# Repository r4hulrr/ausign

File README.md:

# AUSIGN – Real-Time Auslan Sign Language Interpreter

 **Breaking communication barriers** for the Australian Deaf community with an affordable, wearable, real-time Auslan-to-speech translation glove. Check out the [demo video](https://drive.google.com/file/d/1WPN_qFuqe7VqrdAuftsNLOaqI1UlMCOe/view?usp=sharing).

## Overview
**AUSIGN** is a wearable assistive technology device designed to translate **Australian Sign Language (Auslan)** into spoken English **in real time**, enabling smoother and more natural communication for deaf and non-verbal individuals.

Unlike existing ASL-centric devices, AUSIGN is **purpose-built for Auslan**, incorporating contextual awareness via a heart-rate sensor, low-latency audio feedback, and Bluetooth connectivity for flexible output through a mobile/desktop app.

##  Key Features
- **Auslan-specific design** – recognises grammar and gestures unique to Auslan.
- **Context-aware translation** – heartbeat sensing to infer emotional tone.
- **Low-latency output** – low latency translation for natural conversations.
- **Comfort & portability** – under 150 g, designed for all-day wear.
- **Cross-platform UI** – BLE-connected Python GUI.
- **Rechargeable & all-day battery life** – ~6 hours continuous operation.

## System Architecture

**High Level Diagram**

**Hardware**
- **Sensors:**  
  - 5× flex sensors for finger bend detection  
  - LSM6DSOTR 6-axis IMU for hand motion/orientation  
  - MAX30105 heartbeat sensor for emotional context  
- **Processing:** ESP32-S3 microcontroller with BLE & I²S audio output  
- **Output:** OLED display + speaker (via MAX98357A DAC/amp), 2× customisable push buttons  
- **Power:** 3.7 V Li-Po battery with BQ24074 power management & charging

**Software**
- **Firmware:** Reads sensor data, sends via BLE to host app, plays audio from internal flash.  
- **Recognition algorithm:** Condition-matching engine using flex, IMU, and BPM thresholds from CSV definitions.  
- **GUI:** Python-based BLE interface for displaying recognised signs, sensor status, and audio playback.  

## Repository Structure
```
├── firmware/ # ESP32-S3 C++ firmware (Arduino/ESP-IDF)
│ ├── src # Contains the main esp32 code along with test code for every component
│ ├── partitions # Custom partition implemented for our 16MB Flash size
├── gui/ # Python BLE GUI application
│ ├── frontend.py # main GUI script
│ ├── signs.csv # Sign definition mappings
│ └── ...
├── hardware/ # PCB schematics and board layouts
│ ├── main_board/
│ ├── breakout_board/
├── demo # Demo video
│ ├── demo_video.mp4
├── docs/ # design docs
└── LICENSE
└── README.md
```

## Demo
Check out the [demo video](demo/demo_video.mov) to see AUSIGN in action.

## License
This project is licensed under the [MIT License](LICENSE).

## Authors
- **Rahul Ramachandran** 
- **Enzo Moriguchi** 

---
> *“Technology is best when it brings people together.”* – AUSIGN aims to bridge the communication gap and foster inclusion through engineering innovation.

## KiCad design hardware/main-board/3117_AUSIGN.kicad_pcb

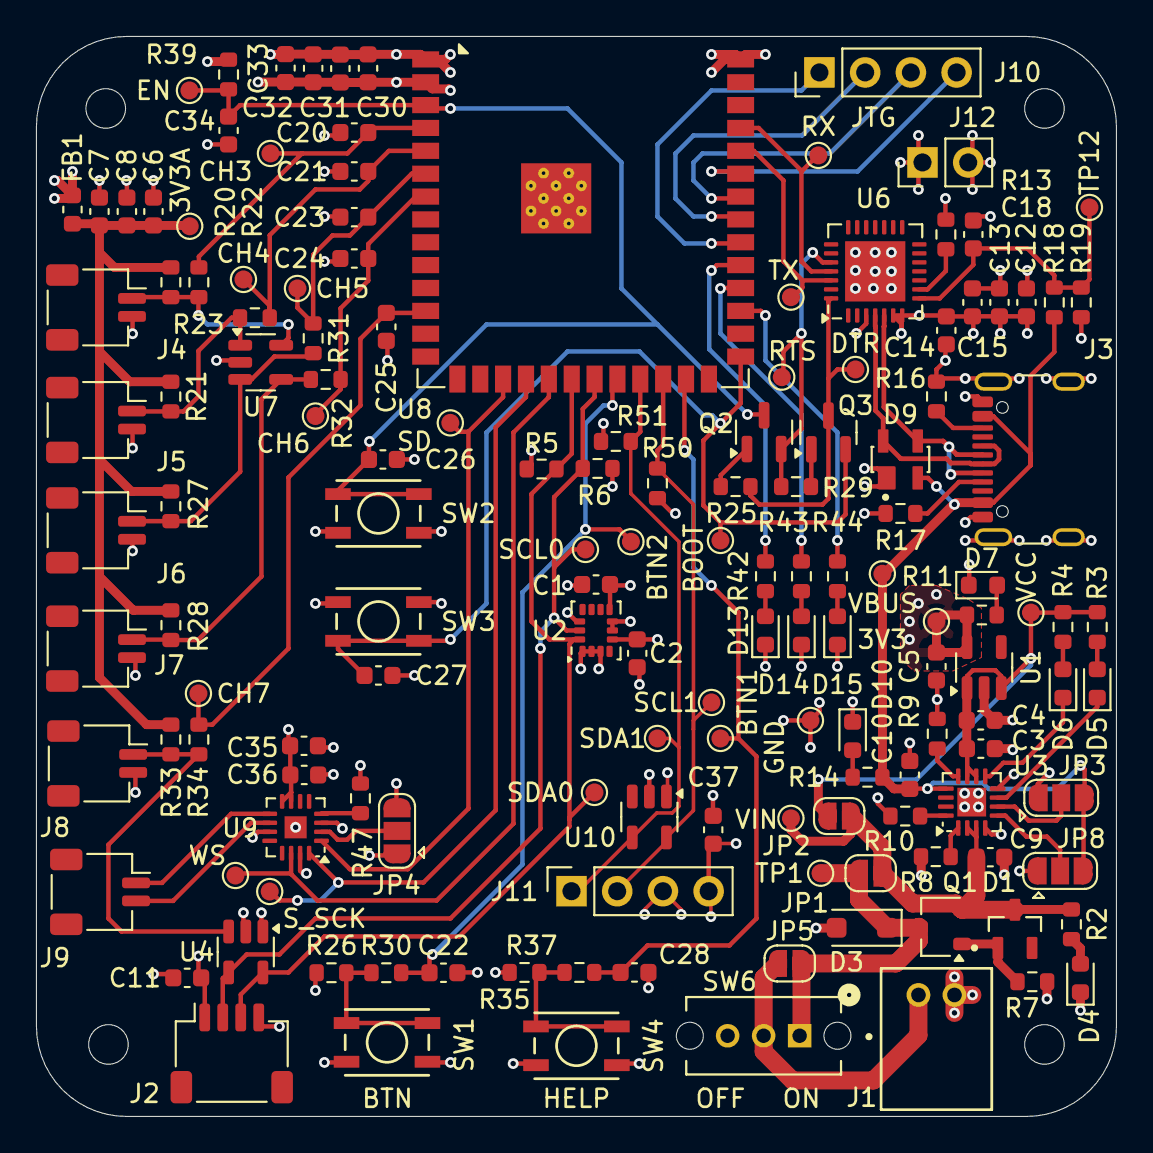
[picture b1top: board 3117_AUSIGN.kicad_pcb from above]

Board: 4 copper layers, 60.0 x 60.0 mm, 151 parts (0 on the bottom side), 70 nets.

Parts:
3V3, 3V3A: TestPoint; TestPoint_Pad_D1.0mm
BOOT: TestPoint; TestPoint_Pad_D1.0mm
BTN1, BTN2: TestPoint; TestPoint_Pad_D1.0mm
C1, C2, C7, C8, C11, C14, C15, C20, C21, C22, C23, C24, C25, C26, C27, C28, C30, C31, C36, C37: 100n; C_0603_1608Metric
C3, C9, C12, C13: 4u7; C_0603_1608Metric
C4, C5, C10, C18, C34: 1u; C_0603_1608Metric
C6, C35: 10u; C_0603_1608Metric
C32, C33: 22u; C_0603_1608Metric
CH3, CH4, CH5, CH6, CH7: TestPoint; TestPoint_Pad_D1.0mm
D1: MMBZ5233BLT1G
D3: SMF5.0A; D_SOD-123F
D4, D7, D10: LTST-C190KGKT; LED_0603_1608Metric
D5, D6, D13, D14, D15: LTST-C190KFKT; LED_0603_1608Metric
D9: SP0503BAHT; SP0503BAHTG
DTR: TestPoint; TestPoint_Pad_D1.0mm
EN: TestPoint; TestPoint_Pad_D1.0mm
FB1: BLM18AG601SN1D; L_0603_1608Metric
GND: TestPoint; TestPoint_Pad_D1.0mm
H1, H2, H3, H4: MountingHole; MountingHole_2.2mm_M2
J1: JST_PH_2P
J2: JST_SH_4P; JST_SH_SM04B-SRSS-TB_1x04-1MP_P1.00mm_Horizontal
J3: USB4105-GF-A; USB_C_Receptacle_GCT_USB4105-xx-A_16P_TopMnt_Horizontal
J4, J5, J6, J7, J8, J9: JST_SH_2P; JST_SH_SM02B-SRSS-TB_1x02-1MP_P1.00mm_Horizontal
J10: Conn_01x04_Pin; PinHeader_1x04_P2.54mm_Vertical
J11: Conn_01x04_Socket; PinSocket_1x04_P2.54mm_Vertical
J12: Conn_01x02_Pin; PinHeader_1x02_P2.54mm_Vertical
JP1, JP2, JP5: SolderJumper_2_Open; SolderJumper-2_P1.3mm_Open_RoundedPad1.0x1.5mm
JP3, JP4, JP8: SolderJumper_3_Open; SolderJumper-3_P1.3mm_Open_RoundedPad1.0x1.5mm
Q1: IRLML6402TRPBF; SOT-23W
Q2, Q3: SS8050; SOT-23
R2, R3, R4: 499; R_0603_1608Metric
R5, R6, R50, R51: 4k7; R_0603_1608Metric
R7: 100k; R_0603_1608Metric
R8, R20, R21, R22, R23, R25, R26, R27, R28, R29, R31, R32, R33, R34, R35, R39: 10k; R_0603_1608Metric
R9, R10: 1.5k; R_0603_1608Metric
R11, R42, R43, R44: 200; R_0603_1608Metric
R13, R14, R30, R37: 1k; R_0603_1608Metric
R16, R17: 5k1; R_0603_1608Metric
R18: 22k1; R_0603_1608Metric
R19: 47k5; R_0603_1608Metric
R47: 634k; R_0603_1608Metric
RTS: TestPoint; TestPoint_Pad_D1.0mm
RX: TestPoint; TestPoint_Pad_D1.0mm
SCL0, SCL1: TestPoint; TestPoint_Pad_D1.0mm
SD: TestPoint; TestPoint_Pad_D1.0mm
SDA0, SDA1: TestPoint; TestPoint_Pad_D1.0mm
SW1, SW2, SW3, SW4: PTS815SJK250SMTR
SW6: OS102011MS2QN1
S_SCK: TestPoint; TestPoint_Pad_D1.0mm
TP1, TP12: TestPoint; TestPoint_Pad_D1.0mm
TX: TestPoint; TestPoint_Pad_D1.0mm
U1: AP2112K-3.3; SOT-23-5
U2: LSM6DSOTR; LGA-14_3x2.5mm_P0.5mm_LayoutBorder3x4y
U3: BQ24074RGT; VQFN-16-1EP_3x3mm_P0.5mm_EP1.6x1.6mm
U4, U7, U10: ESDS314DBVR; SOT-23-5
U6: CP2102N-A02-GQFN28; QFN-28-1EP_5x5mm_P0.5mm_EP3.35x3.35mm
U8: ESP32-S3-WROOM-1
U9: MAX98357A; TQFN-16-1EP_3x3mm_P0.5mm_EP1.23x1.23mm
VBUS: TestPoint; TestPoint_Pad_D1.0mm
VCC: TestPoint; TestPoint_Pad_D1.0mm
VIN: TestPoint; TestPoint_Pad_D1.0mm
WS: TestPoint; TestPoint_Pad_D1.0mm

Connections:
+3V3: 3V3.1, C1.1, C2.1, C5.1, C11.1, C12.1, C13.1, C14.1, C15.1, C30.1, C31.1, C32.1, C33.1, C35.1, C36.1, C37.1, FB1.1, J2.1, J11.4, J12.1, JP4.3 (B), R5.1, R6.1, R11.1, R13.1, R26.1, R35.1, R39.1, R47.1, R50.2, R51.2, U1.5 (VOUT), U2.5 (VDDIO), U2.8 (VDD), U2.12 (CS), U4.1 (I/O1), U6.6 (VDD), U6.7 (VREGIN), U8.2 (3V3), U9.7 (VDD), U9.8 (VDD), U10.1 (I/O1)
+3V3A: 3V3A.1, C6.1, C7.1, C8.1, FB1.2, R20.1, R21.1, R27.1, R28.1, R33.1
ADC1_CH3: C20.1, CH3.1, R22.1, U8.4 (IO4)
ADC1_CH4: C21.1, CH4.1, R23.1, U8.5 (IO5)
ADC1_CH5: C23.1, CH5.1, R31.1, U8.6 (IO6)
ADC1_CH6: C24.1, CH6.1, R32.1, U8.7 (IO7)
ADC1_CH7: C25.1, CH7.1, R34.1, U8.12 (IO8)
BOOT: BOOT.1, C27.1, Q3.2 (E), SW3.2 (B), U8.27 (IO0)
BTN1: BTN1.1, C28.1, R37.1, U8.25 (IO48)
BTN2: BTN2.1, C22.1, R30.1, U8.22 (IO14)
CH3: J4.1, R20.2, R22.2, U7.5 (I/O4)
CH4: J5.1, R21.2, R23.2, U7.1 (I/O1)
CH5: J6.1, R27.2, R31.2, U7.3 (I/O2)
CH6: J7.1, R28.2, R32.2, U7.4 (I/O3)
CH7: J8.1, R33.2, R34.2, U4.3 (I/O2)
DTR: DTR.1, Q3.3 (C), R25.1, U6.28 (~DTR)
EN: C26.1, C34.1, EN.1, Q2.3 (C), R39.2, SW2.2 (B), U8.3 (EN)
GND: C1.2, C2.2, C3.2, C4.2, C5.2, C6.2, C7.2, C8.2, C9.2, C10.2, C11.2, C12.2, C13.2, C14.2, C15.2, C18.2, C20.2, C21.2, C22.2, C23.2, C24.2, C25.2, C26.2, C27.2, C28.2, C30.2, C31.2, C32.2, C33.2, C34.2, C35.2, C36.2, C37.2, D3.2 (A), D4.1 (K), D7.1 (K), D9.1 (A), D10.1 (K), D13.1 (K), D14.1 (K), D15.1 (K), GND.1, J1.2, J2.4, J3.A1 (GND), J3.A12 (GND), J3.B1 (GND), J3.B12 (GND), J3.S1 (SHIELD), J4.2, J5.2, J6.2, J7.2, J8.2, J11.3, J12.2, JP3.1 (A), JP4.1 (A), JP8.1 (A), R7.2, R8.2, R9.2, R10.2, R16.2, R17.2, R19.2, SW1.1 (A), SW2.1 (A), SW3.1 (A), SW4.1 (A), U1.2 (GND), U2.1 (SDO/SA0), U2.2 (SDX), U2.3 (SCX), U2.6 (GND), U2.7 (GND), U3.4 (~CE), U3.8 (VSS), U3.17 (VSS), U4.2 (GND), U6.3 (GND), U6.29 (GND), U7.2 (GND), U8.1 (GND), U8.40 (GND), U8.41 (GND), U9.3 (GND), U9.11 (GND), U9.15 (GND), U9.17 (PAD), U10.2 (GND)
I2C0_SCL: J2.2, R6.2, SCL0.1, U2.13 (SCL), U4.4 (I/O3), U8.21 (IO13)
I2C0_SDA: J2.3, R5.2, SDA0.1, U2.14 (SDA), U4.5 (I/O4), U8.20 (IO12)
I2C1_SCL: J11.2, R50.1, SCL1.1, U8.24 (IO47), U10.5 (I/O4)
I2C1_SDA: J11.1, R51.1, SDA1.1, U8.23 (IO21), U10.4 (I/O3)
I2S_SCK: S_SCK.1, U8.18 (IO10), U9.16 (BCLK)
I2S_SD: SD.1, U8.17 (IO9), U9.1 (DIN)
I2S_WS: U8.19 (IO11), U9.14 (LRCLK), WS.1
LED3: R42.1, U8.31 (IO38)
LED4: R43.1, U8.30 (IO37)
LED5: R44.1, U8.29 (IO36)
unnamed: D1.1 (A), Q1.1 (G), R7.1
unnamed: D3.1 (K), JP1.1 (A), JP5.2 (B), Q1.3 (D), SW6.1 (A), TP1.1
unnamed: D4.2 (A), R2.2
unnamed: D5.2 (A), R3.2
unnamed: D5.1 (K), U3.7 (~PGOOD)
unnamed: D6.2 (A), R4.2
unnamed: D6.1 (K), U3.9 (~CHG)
unnamed: D7.2 (A), R11.2
unnamed: D10.2 (A), R14.2
unnamed: D13.2 (A), R42.2
unnamed: D14.2 (A), R43.2
unnamed: D15.2 (A), R44.2
unnamed: J1.1, JP5.1 (A), SW6.2 (B)
unnamed: J3.A5 (CC1), R17.1
unnamed: J3.B5 (CC2), R16.1
unnamed: J9.1, U9.9 (OUTP)
unnamed: J9.2, U9.10 (OUTN)
unnamed: JP3.2 (C), U3.6 (EN1)
unnamed: JP4.2 (C), U9.2 (GAIN_SLOT)
unnamed: JP8.2 (C), U3.5 (EN2)
unnamed: Q2.1 (B), R25.2
unnamed: Q3.1 (B), R29.2
unnamed: R26.2, R30.2, SW1.2 (B)
unnamed: R35.2, R37.2, SW4.2 (B)
unnamed: R9.1, U3.12 (ILIM)
unnamed: R10.1, U3.16 (ISET)
unnamed: R8.1, U3.1 (TS)
unnamed: C18.1, R18.2, R19.1, TP12.1, U6.8 (VBUS)
unnamed: R13.2, U6.9 (~RST)
unnamed: R47.2, U9.4 (~SD_MODE)
RTS: Q2.2 (E), R29.1, RTS.1, U6.24 (~RTS)
RXD0: RX.1, U6.25 (RXD), U8.37 (TXD0)
TCK: J10.1, U8.32 (IO39)
TDI: J10.3, U8.34 (IO41)
TDO: J10.2, U8.33 (IO40)
TMS: J10.4, U8.35 (IO42)
TXD0: TX.1, U6.26 (TXD), U8.36 (RXD0)
USB_DN: D9.3 (K), J3.A7 (D-), J3.B7 (D-), U6.5 (D-)
USB_DP: D9.4 (K), J3.A6 (D+), J3.B6 (D+), U6.4 (D+)
VBUS: C10.1, D9.2 (K), J3.A4 (VBUS), J3.A9 (VBUS), J3.B4 (VBUS), J3.B9 (VBUS), JP3.3 (B), JP8.3 (B), R14.1, R18.1, U3.13 (IN), VBUS.1
VCC: C3.1, C4.1, JP2.2 (B), R3.1, R4.1, U1.1 (VIN), U1.3 (EN), U3.10 (OUT), U3.11 (OUT), VCC.1
Vin: C9.1, D1.3 (K), JP1.2 (B), JP2.1 (A), Q1.2 (S), R2.1, U3.2 (BAT), U3.3 (BAT), VIN.1

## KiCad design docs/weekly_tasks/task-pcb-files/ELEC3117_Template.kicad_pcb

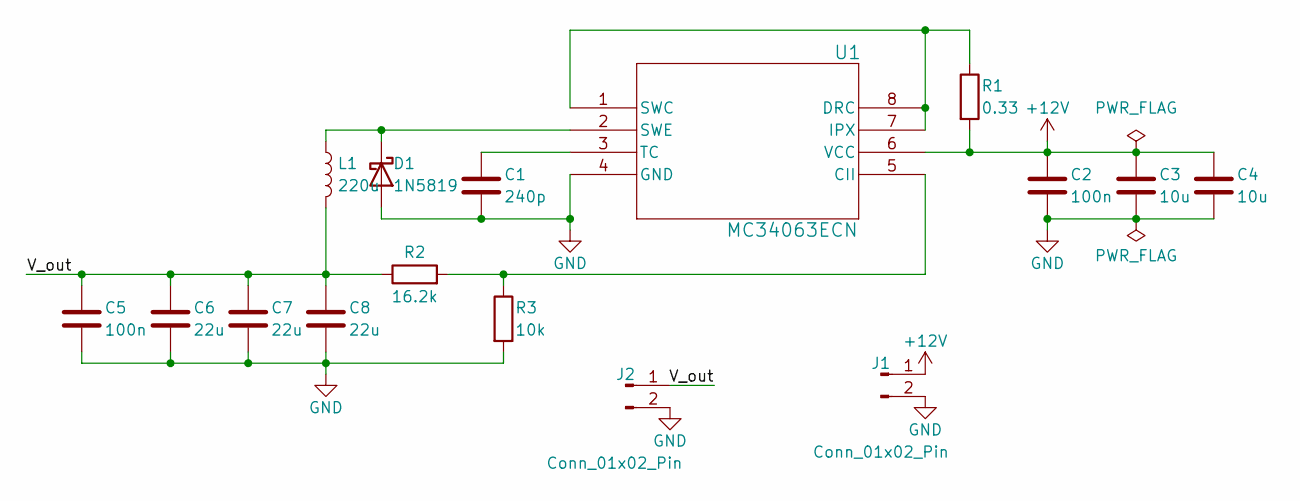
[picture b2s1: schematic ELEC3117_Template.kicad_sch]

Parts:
C1: 240p; C_0805_2012Metric
C2, C5: 100n; C_0805_2012Metric
C3, C4: 10u; C_0805_2012Metric
C6, C7, C8: 22u; C_0805_2012Metric
D1: 1N5819; D_DO-41_SOD81_P10.16mm_Horizontal
J1, J2: Conn_01x02_Pin; PinHeader_1x2_2.54mm_Vertical
L1: 220u; IND_RCH8011_SUM
R1: 0.33; R_0805_2012Metric
R2: 16.2k; R_0805_2012Metric
R3: 10k; R_0805_2012Metric
U1: MC34063ECN; DIP-8_STM

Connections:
+12V: C2.1, C3.1, C4.1, J1.1, R1.2, U1.6 (VCC)
/V_out: C5.1, C6.1, C7.1, C8.1, J2.1, L1.2, R2.1
GND: C1.2, C2.2, C3.2, C4.2, C5.2, C6.2, C7.2, C8.2, D1.2 (A), J1.2, J2.2, R3.2, U1.4 (GND)
unnamed: D1.1 (K), L1.1, U1.2 (SWE)
unnamed: R2.2, R3.1, U1.5 (CII)
unnamed: R1.1, U1.1 (SWC), U1.7 (IPX), U1.8 (DRC)
unnamed: C1.1, U1.3 (TC)

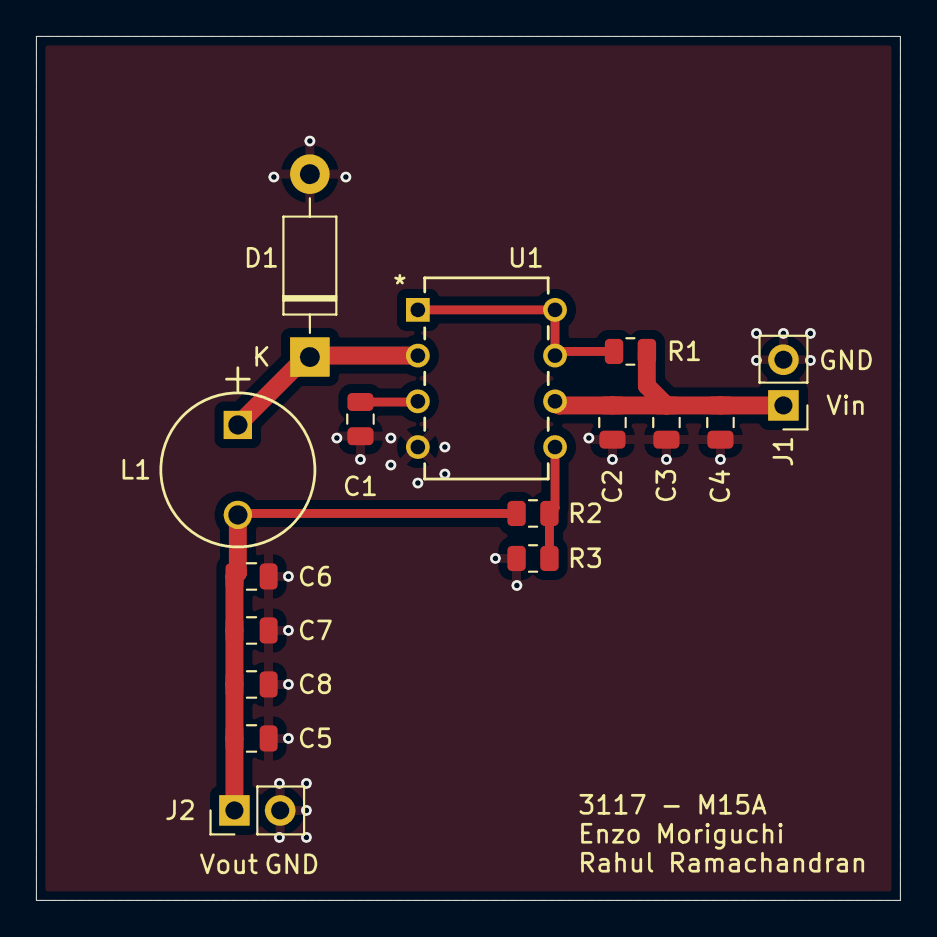
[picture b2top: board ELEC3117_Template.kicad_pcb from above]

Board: 2 copper layers, 48.0 x 48.0 mm, 16 parts (0 on the bottom side), 7 nets.

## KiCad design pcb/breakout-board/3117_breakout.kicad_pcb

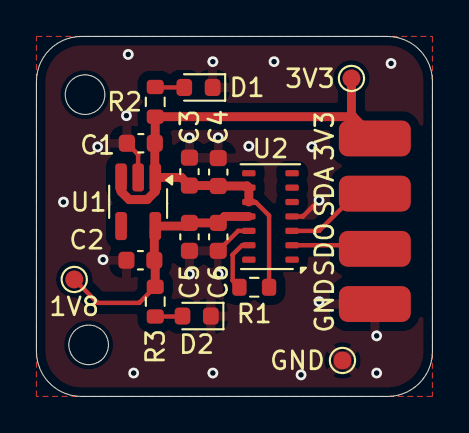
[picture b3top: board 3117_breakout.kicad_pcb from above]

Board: 2 copper layers, 22.0 x 20.0 mm, 19 parts (0 on the bottom side), 8 nets.

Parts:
1V8, 3V3: TestPoint; TestPoint_Pad_D1.0mm
C1: 1u; C_0603_1608Metric
C2: 0.47u; C_0603_1608Metric
C3: 10u; C_0603_1608Metric
C4, C6: 100n; C_0603_1608Metric
C5: 4u7; C_0603_1608Metric
D1: LTST-C190KGKT; LED_0603_1608Metric
D2: 5988E40107F; LED_0603_1608Metric
GND: TestPoint; TestPoint_Pad_D1.0mm
H1, H2: MountingHole; MountingHole_2.2mm_M2
J1: Conn_01x04_Pin; JST_SH_SM04B-SRSS-TB_1x04-1MP_P1.00mm_Horizontal
R1: 4k7; R_0603_1608Metric
R2: 200; R_0603_1608Metric
R3: 49.9; R_0603_1608Metric
U1: TLV77018PDBVR; SOT-23-5_HandSoldering
U2: MAX30102; Maxim_OLGA-14_3.3x5.6mm_P0.8mm

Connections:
+1V8: 1V8.1, C2.1, C5.1, C6.1, R3.1, U1.5 (OUT), U2.11 (VDD)
+3V3: 3V3.1, C1.1, C3.1, C4.1, J1.4, R1.1, R2.1, U1.1 (IN), U1.3 (EN), U2.9 (VLED+), U2.10 (VLED+)
GND: C1.2, C2.2, C3.2, C4.2, C5.2, C6.2, D1.1 (K), D2.1 (K), GND.1, J1.1, U1.2 (GND), U2.4 (PGND), U2.12 (GND)
I2C0_SCL: J1.2, U2.2 (SCL)
I2C0_SDA: J1.3, U2.3 (SDA)
unnamed: D1.2 (A), R2.2
unnamed: D2.2 (A), R3.2
unnamed: R1.2, U2.13 (~INT)

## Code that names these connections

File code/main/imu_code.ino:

// Default Arduino Libraries
#include <Arduino.h>
#include <Wire.h>
#include <SPI.h>
#include <SD.h>

// Libraries to download from Arduino IDE
#include <RTClib.h>
#include <Adafruit_MAX31855.h>
#include <Adafruit_BME280.h>
#include <Adafruit_LSM6DS3TRC.h> // use this for the breakout board
#include <Adafruit_LSM6DSOX.h> // use this for the actual IC

// Constants
#define MAX_READS 2000
#define STORE_ONBOARD_DELAY 5 // In sec
#define PRINT_SAMPLE_DELAY 5 // In sec
#define THERMAL_DELAY 20  // In milliseconds
#define REQUEST_DELAY 100  // In milliseconds
#define OUTPUT_REPEAT_DELAY 15 // In sec
#define SD_OUTPUT_DELAY 1 // In sec
#define SERIAL_SPEED 115200
#define MIN_TEMP -10 
#define MAX_TEMP 10
#define MIN_OUTPUT_REQUESTS 5
#define NUM_BME 4
#define NUM_IMU 2
#define NUM_I2C 2
#define NUM_DIM 3
#define RTC_LINE 0
#define SD_DET_PIN 4
#define SPI1_SO 12
#define SPI1_CSN 9
#define SPI1_SCK 14
#define SPI1_SI 15
#define SPI0_SO 16
#define SPI0_CSN 17
#define SPI0_SCK 18
#define I2C0_SDA 20
#define I2C0_SCL 21 
#define I2C1_SDA 26
#define I2C1_SCL 27 
#define CSN_SD2  13// Select for SD cards, GP22
#define OFFLOAD_TRIGGER 0 // Jumper cable GP12 (Pin 16) to GP13 (Pin 17) to request data offload
#define HEATER_PIN 22 // GP22 (Pin 29)

// Initialise I2C lines
TwoWire TwoWire1 = TwoWire(i2c0, I2C0_SDA, I2C0_SCL);
TwoWire TwoWire2 = TwoWire(i2c1, I2C1_SDA, I2C1_SCL);
TwoWire* Wires[NUM_I2C] = {&TwoWire1 , &TwoWire2};


// Initialise IMUs
Adafruit_LSM6DS3TRC imu[NUM_IMU];
Adafruit_LSM6DSOX imu[NUM_IMU];


TPHReading tphData[NUM_BME][MAX_READS];     // Memory size is NUM_BME * MAX_READS * 3 * 32
AGReading agData[NUM_IMU][MAX_READS];       // Memory size is NUM_IMU * MAX_READS * 6 * 32
double tcData[MAX_READS];                   // Memory size is MAX_READS * 64
DateTime timestamp[MAX_READS];              // Memory size is MAX_READS * 32    -> total is 21 * MAX_READS * 32 bits = 21 * MAX_READS * 4 bytes = 168 kB (for 2000 reads)
bool heaterStatus[MAX_READS];               // Memory size is MAX_READS


void i2cIMUattach() {
  for (int i = 0; i < NUM_IMU; i++) {
    Serial.print(String("Attempt IMU ") + i + String(" ------- "));

    if (!imu[i].begin_I2C((uint8_t)LSM6DS_I2CADDR_DEFAULT, Wires[i])) {
      Serial.println(String("IMU ") + i + String(" not found"));
      successful_setup = false;
    } else {
      Serial.println(String("IMU ") + i + String(" found"));
    }

    imu[i].setAccelRange(LSM6DS_ACCEL_RANGE_2_G);
    imu[i].setGyroRange(LSM6DS_GYRO_RANGE_250_DPS);
    //imu[i].setAccelDataRate(LSM6DS_RATE_12_5_HZ);
    //imu[i].setGyroDataRate(LSM6DS_RATE_12_5_HZ);
  }
}







AGReading getIMUData(int numIMU) {
  sensors_event_t accel_event, gyro_event, temp_event;

  imu[numIMU].getEvent(&(accel_event), &(gyro_event), &(temp_event));

  sensors_vec_t currAcc = accel_event.acceleration;
  sensors_vec_t currGyro = gyro_event.gyro;

  AGReading IMUData = {};

  IMUData.acc[0] = currAcc.x;
  IMUData.acc[1] = currAcc.y;
  IMUData.acc[2] = currAcc.z;
  IMUData.gyro[0] = currGyro.x;
  IMUData.gyro[1] = currGyro.y;
  IMUData.gyro[2] = currGyro.z;

  return IMUData;
}


void printCurrentDataEntry() {
  if (elapsed(millis(), &last_print, PRINT_SAMPLE_DELAY)) {

    for (int i = 0; i < NUM_IMU; i++) {
      Serial.println(String("IMU ") + i + String(" :"));
      Serial.print(agData[i][num_read].acc[0] + String(","));
      Serial.print(agData[i][num_read].acc[1] + String(","));
      Serial.println(agData[i][num_read].acc[2]);
      Serial.print(agData[i][num_read].gyro[0] + String(","));
      Serial.print(agData[i][num_read].gyro[1] + String(","));
      Serial.println(agData[i][num_read].gyro[2]);
    }

    Serial.println(String("Thermo: ") + tcData[num_read]);
    Serial.println(String("Time: ") + String(timestamp[num_read].hour()) + String(":") + String(timestamp[num_read].minute()) + String(":") + String(timestamp[num_read].second()));
  }
}

void outputData() {
  // Output data to serial in CSV format
  Serial.println("Onboard data Formatted as:");
  Serial.println("numread,unixtime,internaltemp,sensornum,temp,pressure,humidity,heaterStatus,accelerationx,accelerationy,accelerationz,gyrox,gyroy,gyroz");
  for (int i = 0; i < num_read; i++) {
    for (int j = 0; j < NUM_BME; j++) {

      Serial.print(agData[j][i].acc[0] + String(","));
      Serial.print(agData[j][i].acc[1] + String(","));
      Serial.print(agData[j][i].acc[2] + String(","));
      Serial.print(agData[j][i].gyro[0] + String(","));
      Serial.print(agData[j][i].gyro[1] + String(","));
      Serial.print(agData[j][i].gyro[2] + String(","));
    }
  }


void setup() {
  Serial.begin(SERIAL_SPEED);
  delay(7500);

  Wires[0]->begin();  // Initialize I2C0
  Wires[1]->begin();  // Initialize I2C1
}


void loop() {
 
}  

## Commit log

2025-06-02 initial draft of survey questions added
2025-06-03 refined draft 1 with concise and appropriate language, as well as adding more content
2025-06-03 added survey results
2025-06-04 made and added all graphs to doc
2025-06-05 added word doc, trimmed a bit
2025-06-05 initial design requirements added
2025-06-05 added intial hld - incomplete, does not have power supply
2025-06-05 added High Level Design and components chosen - still does not include power supply
2025-06-08 market research doc
2025-06-15 Wk2 Project Planning Task uploaded
2025-06-16 initial code commit
2025-06-16 added inital implementation doc
2025-06-16 code for today
2025-06-21 updated hld.io
2025-06-21 updated High Level Design Doc
2025-06-21 final update to hld?
2025-06-22 added power supply pcb report for reference
2025-06-22 created folder for pcb files ref
2025-06-22 created pcb folder
2025-06-22 added inital pcb files
2025-06-23 added ppt and possible script
2025-06-29 added wk4 proj planning task file
2025-07-02 added pitch presentation
2025-07-02 improved pitch
2025-07-03 updated financial plain in pitch
2025-07-10 code for flex sensor added - uses 50 sample average
2025-07-15 added code for scanning i2c devices and heart rate sensor
2025-07-15 four flex sensors along thumb, index, middle and ring finger adc input code added
2025-07-15 possible bluetooth for esp and pc python added - havent tested
2025-07-16 1, 2 and 3 should be interpreted
2025-07-17 code was modified for esp32 wroom as well
2025-07-21 imu code added
2025-07-21 bluetooth for pc started
2025-07-23 added main-board pcb files
2025-07-23 added breakout-board pcb files
2025-07-28 lcd screen code added
2025-07-29 bluetooth works - can receive on pc
2025-07-29 more code for main module
2025-07-29 receives all sensor values onto pc
2025-07-30 play certain sounds when finger bends
2025-07-30 some signs added
2025-07-30 simple sounds and signs added
2025-07-30 possible frontend added
2025-07-30 glove receives ble signal as well, need to fix audio now
2025-07-31 pc plays sounds now
2025-07-31 only robust changes committed
2025-07-31 lcd replaced by lightweight code
2025-07-31 lcd code works if different i2c instance used
2025-07-31 at last lcd works in hand with all other sensors, displays sign received as well
2025-07-31 fixed text orientation and size
2025-07-31 uploaded some wav files to esp32 via littlefs and code to test audio added - havent verified whether speakers works yet
2025-08-01 speaker on this works, tested for a custom wave - still not able to play wav file tho
2025-08-01 speaker can play one if it is converted from wav to array format
2025-08-01 python code to generate pcm raw files added also code for esp32 to play pcm files - not fully working yet
2025-08-01 memory partitioned to include more for little fs, python code ouputs raw PCM and arduino code can play it on speaker clearly - tested
2025-08-01 better flex values and audio
2025-08-01 frontend added with mute button
2025-08-02 new frontend with symbols moved to different files - flex values not reliable rn
2025-08-02 added more symbols
2025-08-03 more symbols with wav files added and uploaded to esp32 memory, but flex sensors need to be fixed
2025-08-04 added code in esp to debug easier for flex; updated frontend to only send signal back if received at least 3 times - avoids incorrect gestures when changing hand signs
2025-08-04 more signs added
2025-08-04 cleaned up code
2025-08-05 should be able to say hello easily now
2025-08-06 couple sentences work now
2025-08-06 imports from csv now
2025-08-06 added exe file
2025-08-07 final code changes - cleaned up code
2025-08-11 cleaned up structure
2025-08-11 added demo video
2025-08-11 fixed small bug in readme
2025-08-11 fixed file extension issue for video file
2025-08-11 updated video link
2025-08-11 small bug fixed
2025-08-11 further updated readme
2025-08-11 updated license
2025-08-11 cleaned up schematic
2025-08-11 added updated high level block diagram
2025-08-11 updated high level block diagram
2025-08-11 added updated block diagram
